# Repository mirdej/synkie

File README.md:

The Synkie is a modular open source analog video processor, developed by Michael Egger, Max Egger and Flo Kaufmann. A bit like the venerable modular Moog synthesizer it lets you toy around with the signal using patch cables – but this time not producing sound but images. It is an instrument for video, a playground, a platform to explore new ways to transform a video signal. Synkie is still in development, we constantly develop new modules – and even the base specifications may still change over time. 

Synkie’s main goal is playability not image quality, even though we try to design each module as best as we can. But patching is done with 2mm laboratory cables – not shielded 75Ohm BNC cables as one would normally use for video. No, you can even use any blank wire and tinker around with the signal in real time on the sk90-breadboard module… The laboratory plugs can be stacked, so you can easily divide the signal into multiple paths, feeding multiple modules at once and change the configuration on the fly. The resulting image can get quite messy down the road, but that’s part of the fun, or maybe even the main purpose…

# Before building stuff from here yourself - read this:

This Github repository is our working space and not a DIY tutorial. Lots of stuff is completely outdated and/or poorly documented. Here are some important notes about the current state of things (Oct 2021):

- Pretty much everything in the EAGLE directory is totally obsolete and we only keep it for documentation.

- We settled on the LMH6643 as our Opamp of choice for almost everything where frequency response matters. Not all schematics reflect this. In most cases if there's an opamp named "generic opamp" or even "LM833" - we probably meant LMH6643.

- There are several modules where the supply connector is flipped. As we etch a lot of boards ourselves there is no silkscreen and we don't see the error. ALWAYS check the polarity !

- We live in PAL land. These modules have not beent tested with NTSC video. Some might need to be adapted slightly, some might even work better than here ;-)

If you have any questions contact <info@synkie.net>

# Basics

## Synkie Backbone
Modules sk000 to sk009 constitute the Synkie Backbone – handling Ins out Outs to the normal Video World. Input video is clamped (black level = GND) and stripped of timing signals and color burst. This signal can then be fed to any processing modules.
In the end , timing signals and a phase corrected color burst is cut back into the modified signal, in sync with the Genlock input.

### sk000-power
Power distribution to backbone modules and rack. +5V, GND, -5V.

### sk001-genlock-in

This module takes any standard video signal as input and generates all necessary timing signals for the Synkie system. The input is first backporch-clamped to GND and all active video is cut off. This black image can serve as a genlock for connected sources (cameras). Colorburst is output as a seperate signal and used to syncronise a quartz crystal that generates a continuous 4.4336Mhz subcarrier signal for the rgb modules. A LM1881 generates the digital sync signals: horizontal sync, vertical sync, backporch and odd/even.

### sk002-input

This modules takes any standard video signal, clamps black level to GND and strips off synctips and colorburst. (still in active debate: me thinks sk002 should apply a gain of 1.43 to bring the 0.7V white level up to 1V)

### sk003-output

This module takes any signal as its input (from DC to 10Mhz). The scale-bias section controls amplitude and dc-shift. The signal is then clipped hard between 0V and 1V. Finally the resyncer adds synctips and colorburst to make it look like a standard video signal. 
When using video as an input to the sk003 any processing beforehand can add some tiny delay - depending on how many modules the signal passes through -  which causes a phase shift in the signal that can alter or completely destroy color. That is why the burst signal from sk001 first goes through a sk004-burstshift (allpass filter) that lets correct the phase error before it gets cut back into the video signal.

## Synkie Signals

### Terminology
| Signal name | Waveform| Description  |Specs|
|---|---|---|---|
|Genlock||A video signal that serves as the master synchronisation signal. Can be routed through and used as an input.|-0.3V to 0.7V|
|Video||Standard PAL video signal|-0.3V to 0.7V|
|Sync| |Digital sync pulses: H-Sync, V-Sync, Backporch, Odd/Even|0V to 5V|
|Burst|| Colorburst only, AC coupled|ca. -0.1V to 0.1V|
|Siff| |Synkie signal. Can be anything, DC, CV, Audio or Video. 0V means black. 1V means white|-1V to 1V|

### The SIFF signal
Synkie's goal is to be able to mix all signals, be it control signals, audio or picture. You should be able to use a video image as control voltage for a VCO like you should be able to inject a sound into the video or watch a steady 0.256 volts.

* Siff signals are DC coupled. 0V means black. 1V means white.
* Siff signals can still be negative, meaning superblack or substracting signals !
* Siff signals can be loud - going beyond 1V and below -1V. The sk003-output module will finally limit the signal to 0-1V.
* Siff signals can range from DC (0Hz) to ca. 10Mhz

This has the following implications for synkie modules:

* All module inputs should be high-impedance, DC coupled and ESR protected.
* All module outputs should be low-impedance and DC coupled.
* Whenever possible a module's bandwidth should be at least 4Mhz
* Sensible CV range should be between 0V and 1V.
* But: Modules must be able to cope with voltages as low as -5V to as high as 5V
* Gate signals are 0V to 1V !!
* So: trigger inputs should trigger at around 0.5V ! Use comparators.

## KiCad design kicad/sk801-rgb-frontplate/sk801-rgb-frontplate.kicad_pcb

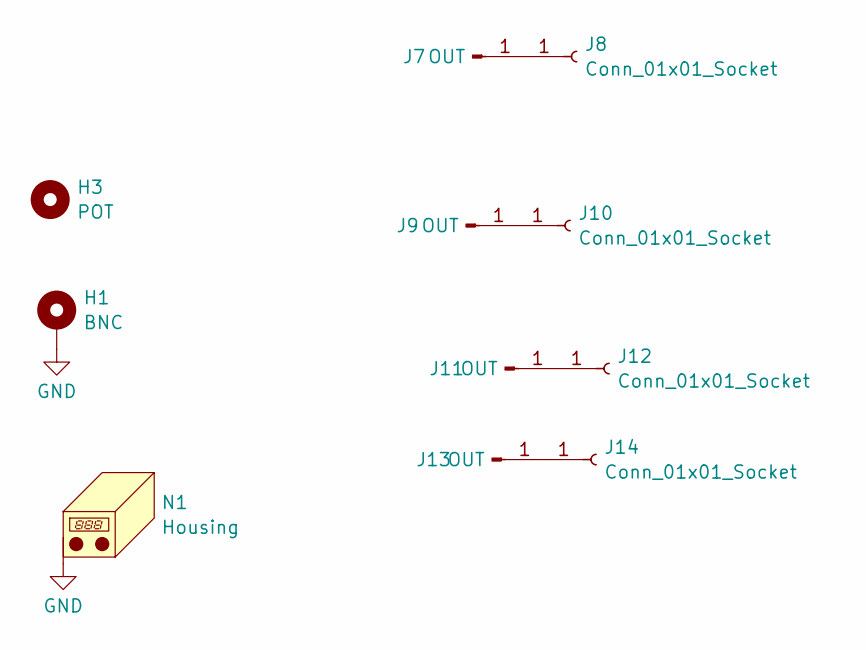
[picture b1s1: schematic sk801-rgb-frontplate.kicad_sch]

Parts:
H1: BNC; BNC_Ali_Frontplate
H3: POT; PotentiometerNournsPRS12Frontplate
J7, J9, J11, J13: OUT; Banana2mm-Löthülse
J8, J10, J12, J14: Conn_01x01_Socket; smd-1pin
N1: Housing; Frontplate_20mm

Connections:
GND: H1.1 (1_1), N1.1 (PAD_1)
unnamed: J7.1 (Pin_1_1), J8.1 (Pin_1_1)
unnamed: J9.1 (Pin_1_1), J10.1 (Pin_1_1)
unnamed: J11.1 (Pin_1_1), J12.1 (Pin_1_1)
unnamed: J13.1 (Pin_1_1), J14.1 (Pin_1_1)

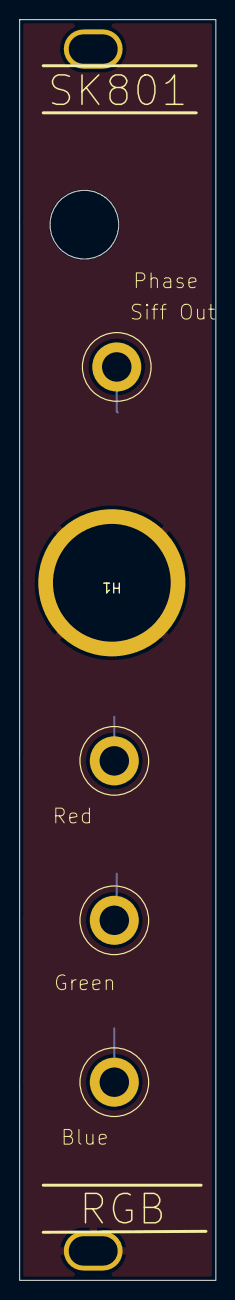
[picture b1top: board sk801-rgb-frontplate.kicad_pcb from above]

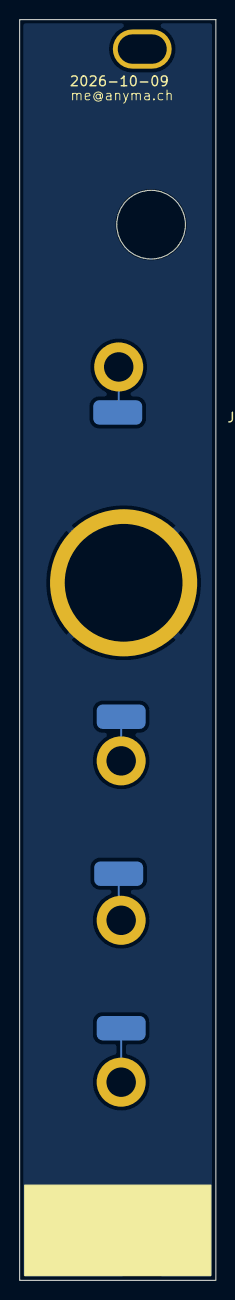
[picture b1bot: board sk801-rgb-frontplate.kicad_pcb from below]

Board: 2 copper layers, 20.0 x 128.5 mm, 11 parts (4 on the bottom side), 5 nets.

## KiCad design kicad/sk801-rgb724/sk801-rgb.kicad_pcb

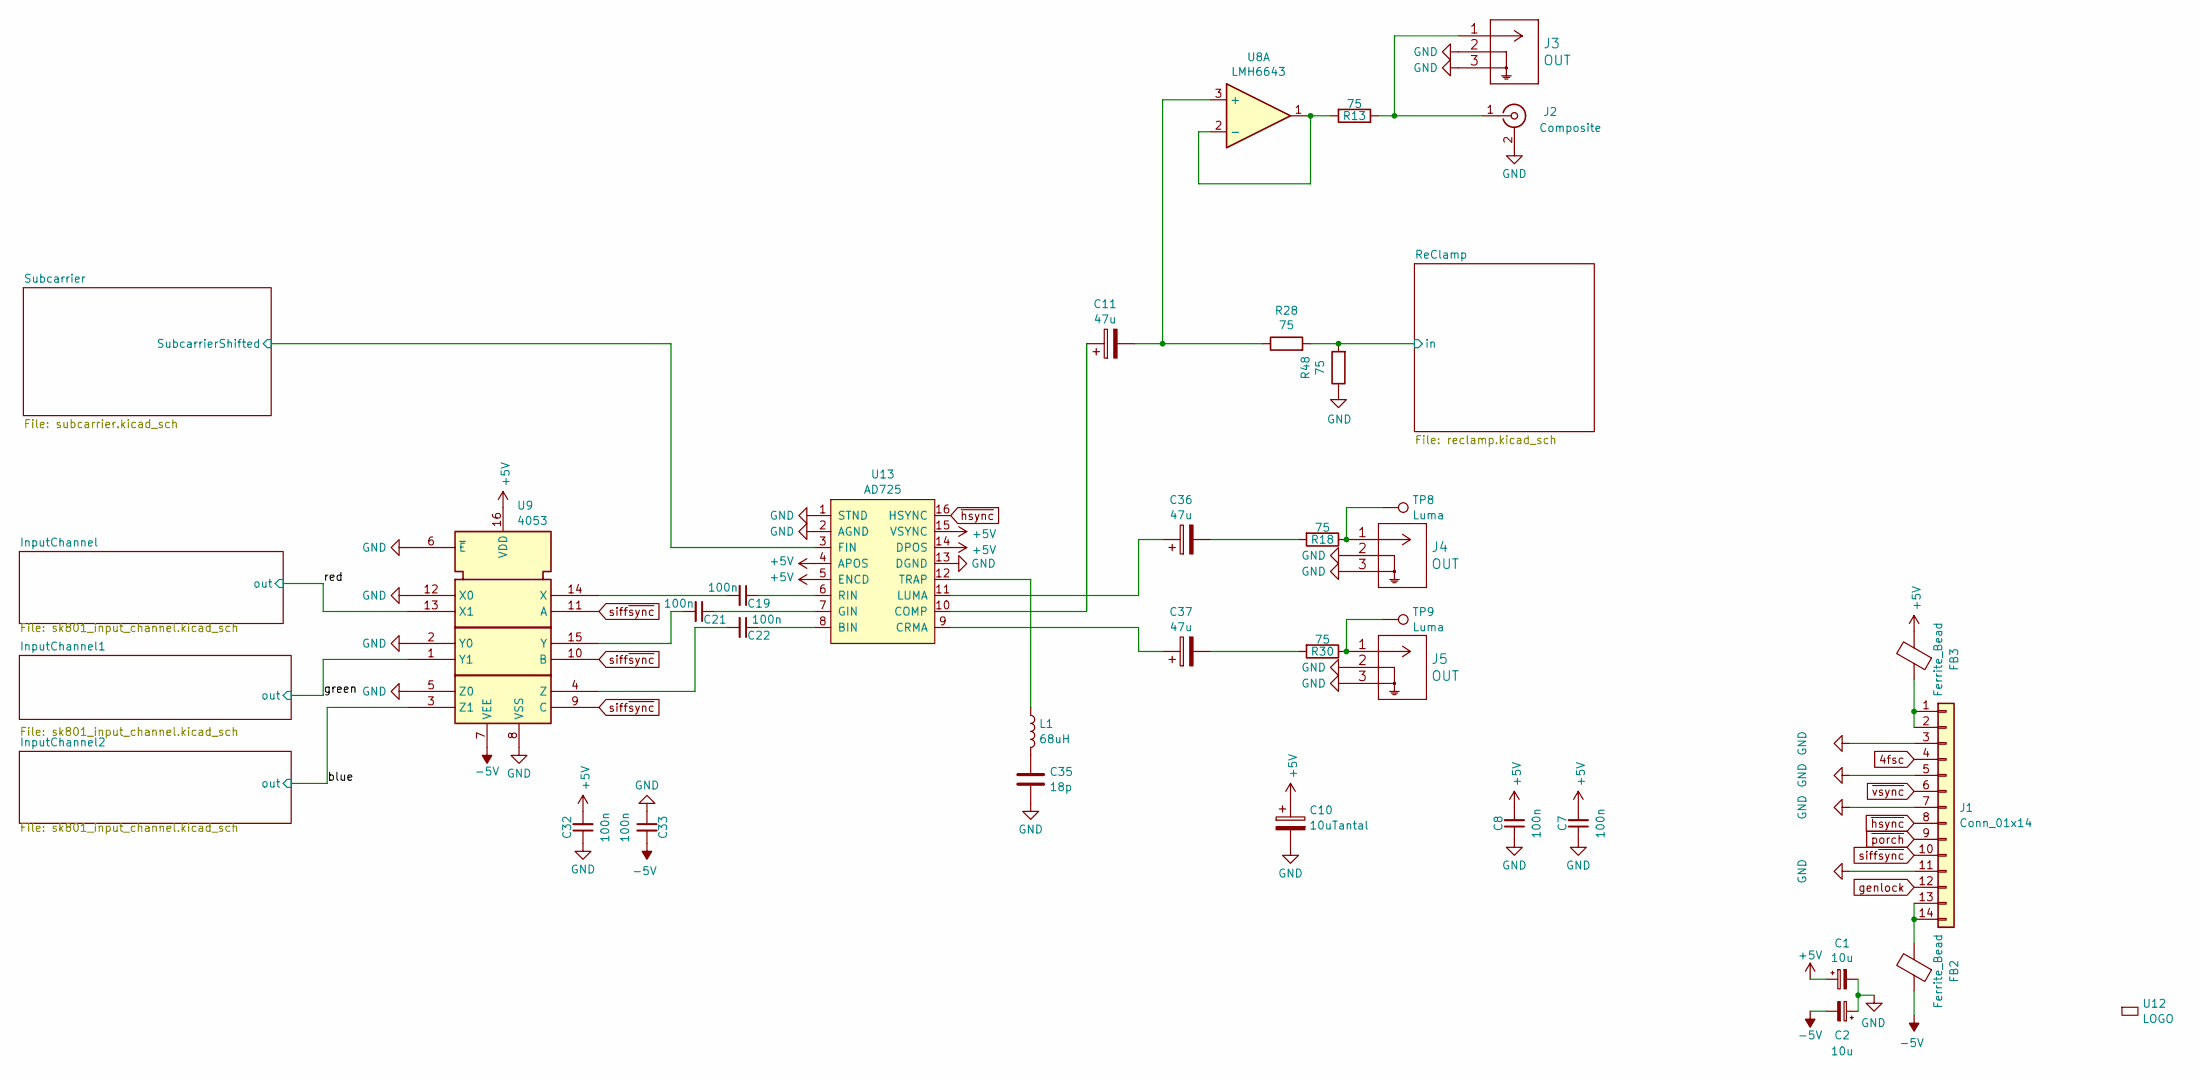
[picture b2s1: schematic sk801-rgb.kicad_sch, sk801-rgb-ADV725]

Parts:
C1, C2: 10u; C_0805_2012Metric; LCSC C15850
C7, C8, C19, C21, C22, C32, C33: 100n; C_0402_1005Metric; LCSC C1525
C10: 10uTantal; CP_EIA-3216-18_Kemet-A; LCSC C7171
C11, C36, C37: 47u; C_1206_3216Metric; LCSC C96123
C35: 18p; C_0603_1608Metric; LCSC C1647
FB2, FB3: Ferrite_Bead; L_0805_2012Metric; LCSC C1017
J1: Conn_01x14; SYNKIE-BUS.v3
J2: Composite; BNC_Aliexpress
J3, J4, J5: OUT; TE_UMCC_2337019-1; LCSC C5137195
L1: 68uH; L_APV_APH0420; LCSC C2929423
R13, R18, R28, R30, R48: 75; R_0603_1608Metric; LCSC C4275
TP8, TP9: Luma; TestPoint_THTPad_D4.0mm_Drill2.0mm
U8: LMH6643; VSSOP-8_3x3mm_P0.65mm; LCSC C478382
U9: 4053; SOIC-16_3.9x9.9mm_P1.27mm; LCSC C7500846
U12: LOGO; logo_anyma
U13: AD725; SOIC-16W_7.5x10.3mm_P1.27mm

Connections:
4fsc: J1.4; also elsewhere on the board
+5V: C1.1, C7.2, C8.2, C10.1, C32.2, FB3.2, U9.16 (VDD), U13.4 (APOS), U13.5 (ENCD), U13.14 (DPOS), U13.15 (VSYNC); also elsewhere on the board
-5V: C2.2, C33.2, FB2.1, U9.7 (VEE); also elsewhere on the board
/ReClamp/in: R28.2, R48.2; also elsewhere on the board
/Subcarrier/SubcarrierShifted: U13.3 (FIN); also elsewhere on the board
/blue: U9.3 (Z1); also elsewhere on the board
/green: U9.1 (Y1); also elsewhere on the board
/red: U9.13 (X1); also elsewhere on the board
GND: C1.2, C2.1, C7.1, C8.1, C10.2, C32.1, C33.1, C35.2, J1.3, J1.5, J1.7, J1.11, J2.2 (Ext), J3.2, J3.3, J4.2, J4.3, J5.2, J5.3, R48.1, U9.2 (Y0), U9.5 (Z0), U9.6 (~E), U9.8 (VSS), U9.12 (X0), U13.1 (STND), U13.2 (AGND), U13.13 (DGND); also elsewhere on the board
unnamed: C35.1, L1.2
unnamed: C36.2, R18.2
unnamed: C37.2, R30.2
unnamed: FB3.1, J1.1, J1.2
unnamed: FB2.2, J1.13, J1.14
unnamed: J2.1 (In), J3.1, R13.1
unnamed: J4.1, R18.1, TP8.1 (1_1)
unnamed: J5.1, R30.1, TP9.1 (1_1)
unnamed: C11.2, R28.1, U8.3 (+)
unnamed: R13.2, U8.1, U8.2 (-)
unnamed: C19.2, U9.14 (X)
unnamed: C21.2, U9.15 (Y)
unnamed: C22.2, U9.4 (Z)
unnamed: C22.1, U13.8 (BIN)
unnamed: C11.1, U13.10 (COMP)
unnamed: C37.1, U13.9 (CRMA)
unnamed: C21.1, U13.7 (GIN)
unnamed: C36.1, U13.11 (LUMA)
unnamed: C19.1, U13.6 (RIN)
unnamed: L1.1, U13.12 (TRAP)
genlock: J1.12
siff~sync: J1.10, U9.9 (C), U9.10 (B), U9.11 (A); also elsewhere on the board
~hsync: J1.8, U13.16 (HSYNC)
~porch: J1.9; also elsewhere on the board
~vsync: J1.6

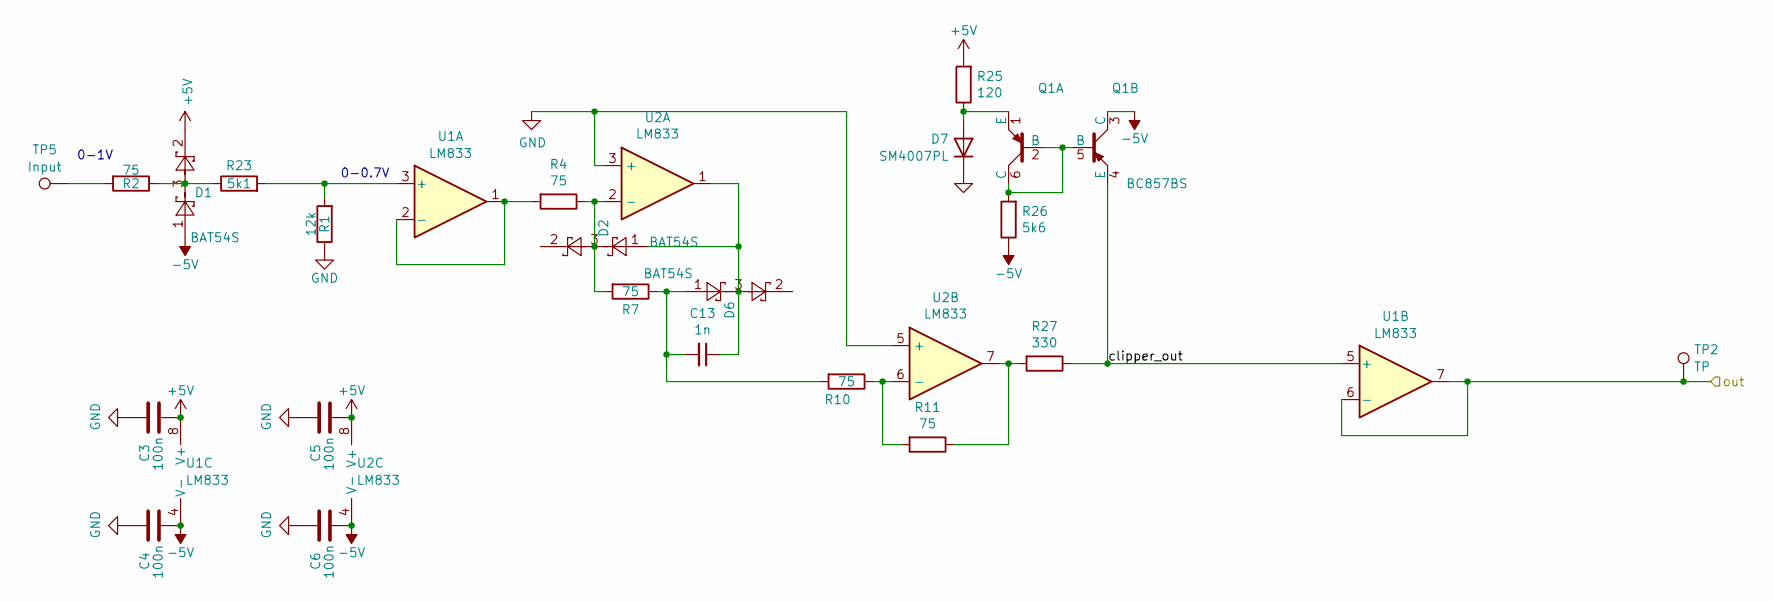
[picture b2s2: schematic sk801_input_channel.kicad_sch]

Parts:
C3, C4, C5, C6: 100n; C_0402_1005Metric; LCSC C1525
C13: 1n; C_0603_1608Metric; LCSC C1588
D1, D2, D6: BAT54S; SOT-23; LCSC C7420333
D7: SM4007PL; D_SOD-123F; LCSC C64898
Q1: BC857BS; SOT-363_SC-70-6_Handsoldering; LCSC C22381405
R1: 12k; R_0603_1608Metric; LCSC C22790
R2, R4, R7, R10, R11: 75; R_0603_1608Metric; LCSC C4275
R23: 5k1; R_0603_1608Metric; LCSC C23186
R25: 120; R_0603_1608Metric; LCSC C22787
R26: 5k6; R_0603_1608Metric; LCSC C23189
R27: 330; R_0603_1608Metric; LCSC C23138
TP2: TP; TestPoint_Pad_D2.0mm
TP5: Input; TestPoint_THTPad_D4.0mm_Drill2.0mm
U1, U2: LM833; SOIC-8_3.9x4.9mm_P1.27mm; LCSC C7969

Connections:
+5V: C3.2, C5.2, D1.2, R25.2, U1.8 (V+), U2.8 (V+); also elsewhere on the board
-5V: C4.2, C6.2, D1.1, Q1.3 (C), R26.1, U1.4 (V-), U2.4 (V-); also elsewhere on the board
/InputChannel/clipper_out: Q1.4 (E), R27.1, U1.5 (+)
/red: TP2.1 (1_1), U1.6 (-), U1.7; also elsewhere on the board
GND: C3.1, C4.1, C5.1, C6.1, D7.1 (K), R1.1, U2.3 (+), U2.5 (+); also elsewhere on the board
unnamed: C13.1, D2.1, D6.3, U2.1
unnamed: C13.2, D6.1, R7.1, R10.2
unnamed: D1.3, R2.1, R23.1
unnamed: D7.2 (A), Q1.1 (E), R25.1
unnamed: Q1.2 (B), Q1.5 (B), Q1.6 (C), R26.2
unnamed: R2.2, TP5.1 (1_1)
unnamed: R11.1, R27.2, U2.7
unnamed: R1.2, R23.2, U1.3 (+)
unnamed: R4.2, U1.1, U1.2 (-)
unnamed: D2.3, R4.1, R7.2, U2.2 (-)
unnamed: R10.1, R11.2, U2.6 (-)

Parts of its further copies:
C14, C15, C16, C18, C25, C26, C27, C28: 100n; C_0402_1005Metric; LCSC C1525
C23, C30: 1n; C_0603_1608Metric; LCSC C1588
D3, D4, D5, D8, D10, D11: BAT54S; SOT-23; LCSC C7420333
D9, D12: SM4007PL; D_SOD-123F; LCSC C64898
Q2, Q3: BC857BS; SOT-363_SC-70-6_Handsoldering; LCSC C22381405
R5, R16: 12k; R_0603_1608Metric; LCSC C22790
R6, R9, R12, R14, R15, R17, R19, R20, R21, R22: 75; R_0603_1608Metric; LCSC C4275
R24, R42: 5k1; R_0603_1608Metric; LCSC C23186
R37, R43: 120; R_0603_1608Metric; LCSC C22787
R38, R44: 5k6; R_0603_1608Metric; LCSC C23189
R39, R45: 330; R_0603_1608Metric; LCSC C23138
TP3, TP4: TP; TestPoint_Pad_D2.0mm
TP6, TP7: Input; TestPoint_THTPad_D4.0mm_Drill2.0mm
U3, U5, U6, U7: LM833; SOIC-8_3.9x4.9mm_P1.27mm; LCSC C7969

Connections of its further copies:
+5V: C14.2, C16.2, C25.2, C27.2, D3.2, D5.2, R37.2, R43.2, U3.8 (V+), U5.8 (V+), U6.8 (V+), U7.8 (V+); also elsewhere on the board
-5V: C15.2, C18.2, C26.2, C28.2, D3.1, D5.1, Q2.3 (C), Q3.3 (C), R38.1, R44.1, U3.4 (V-), U5.4 (V-), U6.4 (V-), U7.4 (V-); also elsewhere on the board
/InputChannel1/clipper_out: Q2.4 (E), R39.1, U3.5 (+)
/InputChannel2/clipper_out: Q3.4 (E), R45.1, U6.5 (+)
/blue: TP4.1 (1_1), U6.6 (-), U6.7; also elsewhere on the board
/green: TP3.1 (1_1), U3.6 (-), U3.7; also elsewhere on the board
GND: C14.1, C15.1, C16.1, C18.1, C25.1, C26.1, C27.1, C28.1, D9.1 (K), D12.1 (K), R5.1, R16.1, U5.3 (+), U5.5 (+), U7.3 (+), U7.5 (+); also elsewhere on the board
unnamed: C23.1, D4.1, D8.3, U5.1
unnamed: C23.2, D8.1, R12.1, R14.2
unnamed: C30.1, D10.1, D11.3, U7.1
unnamed: C30.2, D11.1, R20.1, R21.2
unnamed: D3.3, R6.1, R24.1
unnamed: D5.3, R17.1, R42.1
unnamed: D9.2 (A), Q2.1 (E), R37.1
unnamed: D12.2 (A), Q3.1 (E), R43.1
unnamed: Q2.2 (B), Q2.5 (B), Q2.6 (C), R38.2
unnamed: Q3.2 (B), Q3.5 (B), Q3.6 (C), R44.2
unnamed: R6.2, TP6.1 (1_1)
unnamed: R15.1, R39.2, U5.7
unnamed: R17.2, TP7.1 (1_1)
unnamed: R22.1, R45.2, U7.7
unnamed: R5.2, R24.2, U3.3 (+)
unnamed: R9.2, U3.1, U3.2 (-)
unnamed: D4.3, R9.1, R12.2, U5.2 (-)
unnamed: R14.1, R15.2, U5.6 (-)
unnamed: R16.2, R42.2, U6.3 (+)
unnamed: R19.2, U6.1, U6.2 (-)
unnamed: D10.3, R19.1, R20.2, U7.2 (-)
unnamed: R21.1, R22.2, U7.6 (-)

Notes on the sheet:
0-0.7V
0-1V

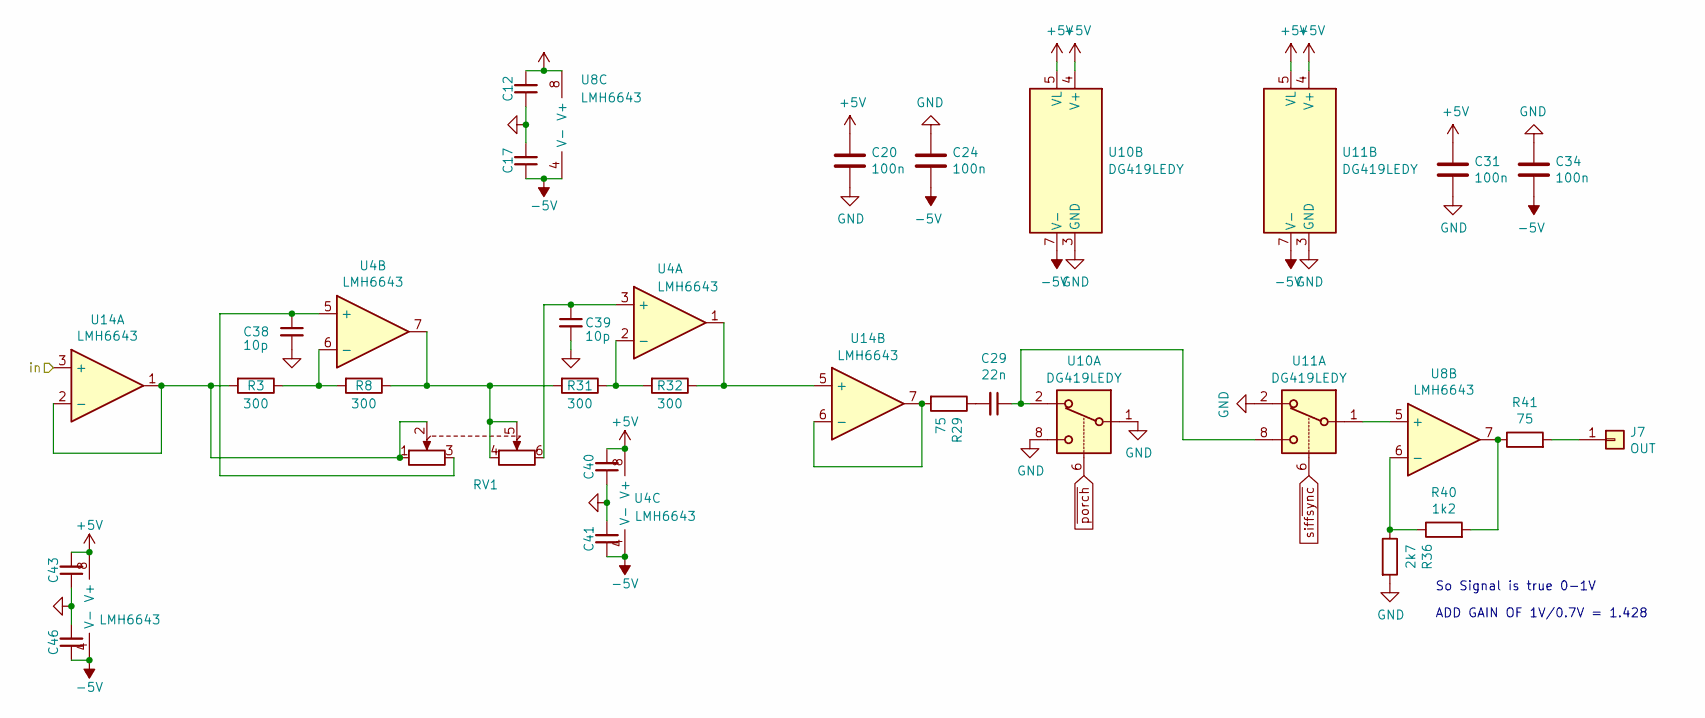
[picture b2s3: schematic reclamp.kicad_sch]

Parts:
C12, C17, C20, C24, C31, C34, C40, C41, C43, C46: 100n; C_0402_1005Metric; LCSC C1525
C29: 22n; C_0603_1608Metric; LCSC C21122
C38, C39: 10p; C_0603_1608Metric; LCSC C1634
J7: OUT; TestPoint_THTPad_D4.0mm_Drill2.0mm
R3, R8, R31, R32: 300; R_0603_1608Metric; LCSC C23025
R29, R41: 75; R_0603_1608Metric; LCSC C4275
R36: 2k7; R_0603_1608Metric; LCSC C13167
R40: 1k2; R_0603_1608Metric; LCSC C22765
RV1: PRS12R-2
U4, U8, U14: LMH6643; VSSOP-8_3x3mm_P0.65mm; LCSC C478382
U10, U11: DG419LEDY; SOIC-8_3.9x4.9mm_P1.27mm; LCSC C2673265

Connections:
+5V: C12.2, C20.1, C31.1, C40.2, C43.2, U4.8 (V+), U8.8 (V+), U10.4 (V+), U10.5 (VL), U11.4 (V+), U11.5 (VL), U14.8 (V+); also elsewhere on the board
-5V: C17.1, C24.2, C34.2, C41.1, C46.1, U4.4 (V-), U8.4 (V-), U10.7 (V-), U11.7 (V-), U14.4 (V-); also elsewhere on the board
/ReClamp/in: U14.3 (+); also elsewhere on the board
GND: C12.1, C17.2, C20.2, C24.1, C31.2, C34.1, C38.2, C39.2, C40.1, C41.2, C43.1, C46.2, R36.2, U10.1, U10.3 (GND), U10.8, U11.2, U11.3 (GND); also elsewhere on the board
unnamed: C29.1, U10.2, U11.8
unnamed: C29.2, R29.1
unnamed: J7.1 (Pin_1_1), R41.2
unnamed: R8.1, R31.2, RV1.4, RV1.5, U4.7
unnamed: R40.2, R41.1, U8.7
unnamed: C39.1, RV1.6, U4.3 (+)
unnamed: R31.1, R32.2, U4.2 (-)
unnamed: C38.1, RV1.3, U4.5 (+)
unnamed: R3.1, R8.2, U4.6 (-)
unnamed: U8.5 (+), U11.1
unnamed: R36.1, R40.1, U8.6 (-)
unnamed: R3.2, RV1.1, RV1.2, U14.1, U14.2 (-)
unnamed: R32.1, U4.1, U14.5 (+)
unnamed: R29.2, U14.6 (-), U14.7
siff~sync: U11.6; also elsewhere on the board
~porch: U10.6; also elsewhere on the board

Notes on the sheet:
ADD GAIN OF 1V/0.7V = 1.428
So Signal is true 0-1V

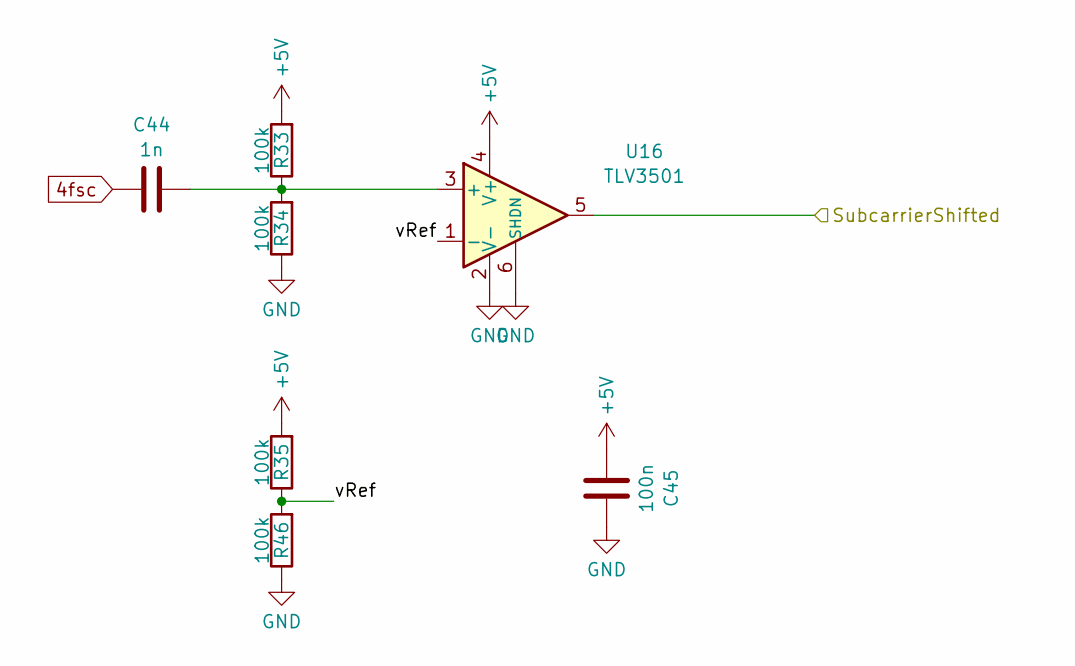
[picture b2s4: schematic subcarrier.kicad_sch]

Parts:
C44: 1n; C_0603_1608Metric; LCSC C1588
C45: 100n; C_0402_1005Metric; LCSC C1525
R33, R34, R35, R46: 100k; R_0603_1608Metric; LCSC C25803
U16: TLV3501; SOT-23-6; LCSC C133251

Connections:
4fsc: C44.1; also elsewhere on the board
+5V: C45.1, R33.2, R35.2, U16.4 (V+); also elsewhere on the board
/Subcarrier/SubcarrierShifted: U16.5; also elsewhere on the board
/Subcarrier/vRef: R35.1, R46.2, U16.1 (-)
GND: C45.2, R34.1, R46.1, U16.2 (V-), U16.6 (SHDN); also elsewhere on the board
unnamed: C44.2, R33.1, R34.2, U16.3 (+)

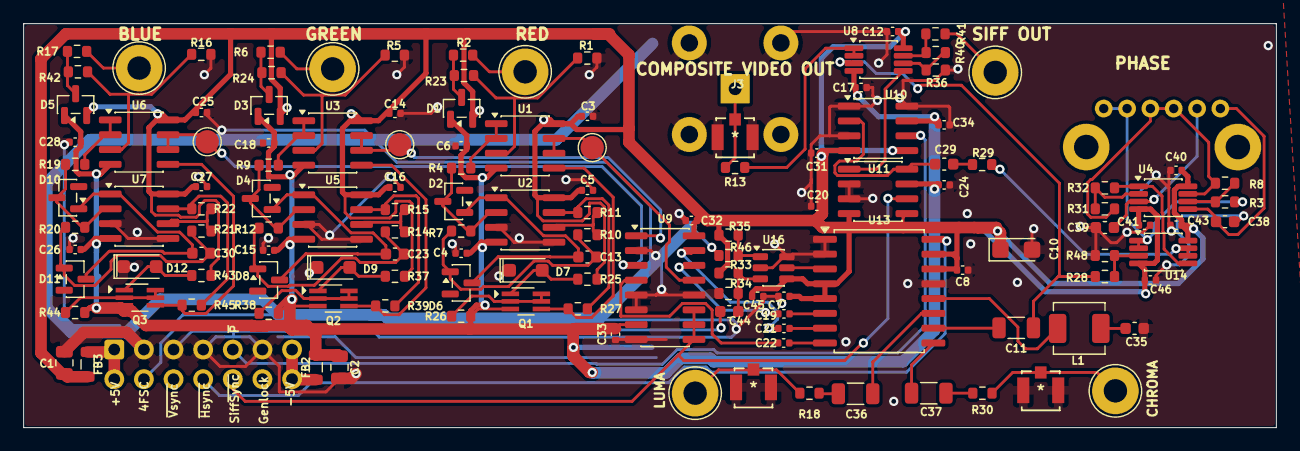
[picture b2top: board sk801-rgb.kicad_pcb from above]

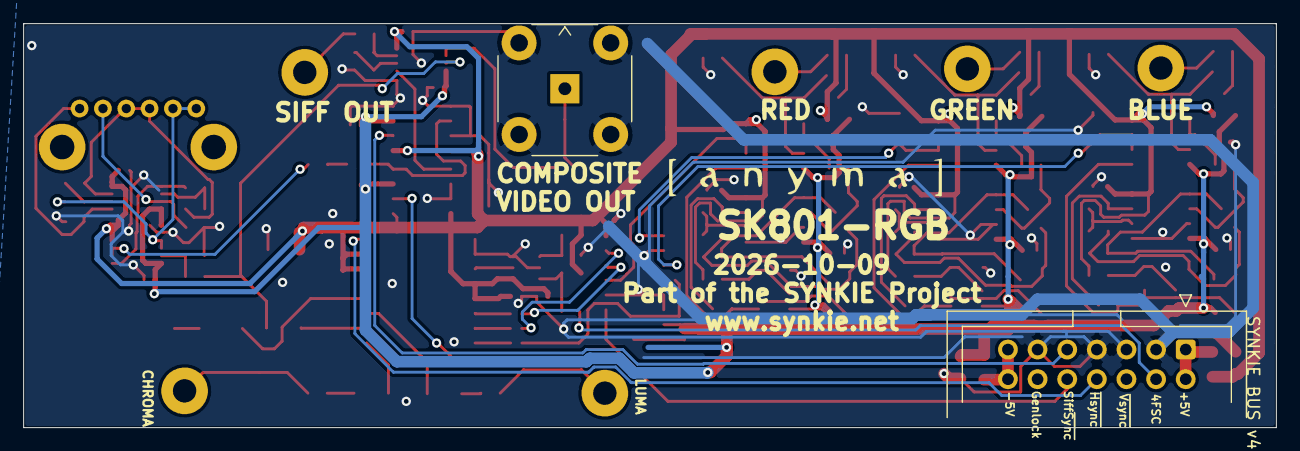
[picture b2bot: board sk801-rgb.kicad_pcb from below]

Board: 2 copper layers, 107.4 x 34.6 mm, 139 parts (4 on the bottom side), 84 nets.

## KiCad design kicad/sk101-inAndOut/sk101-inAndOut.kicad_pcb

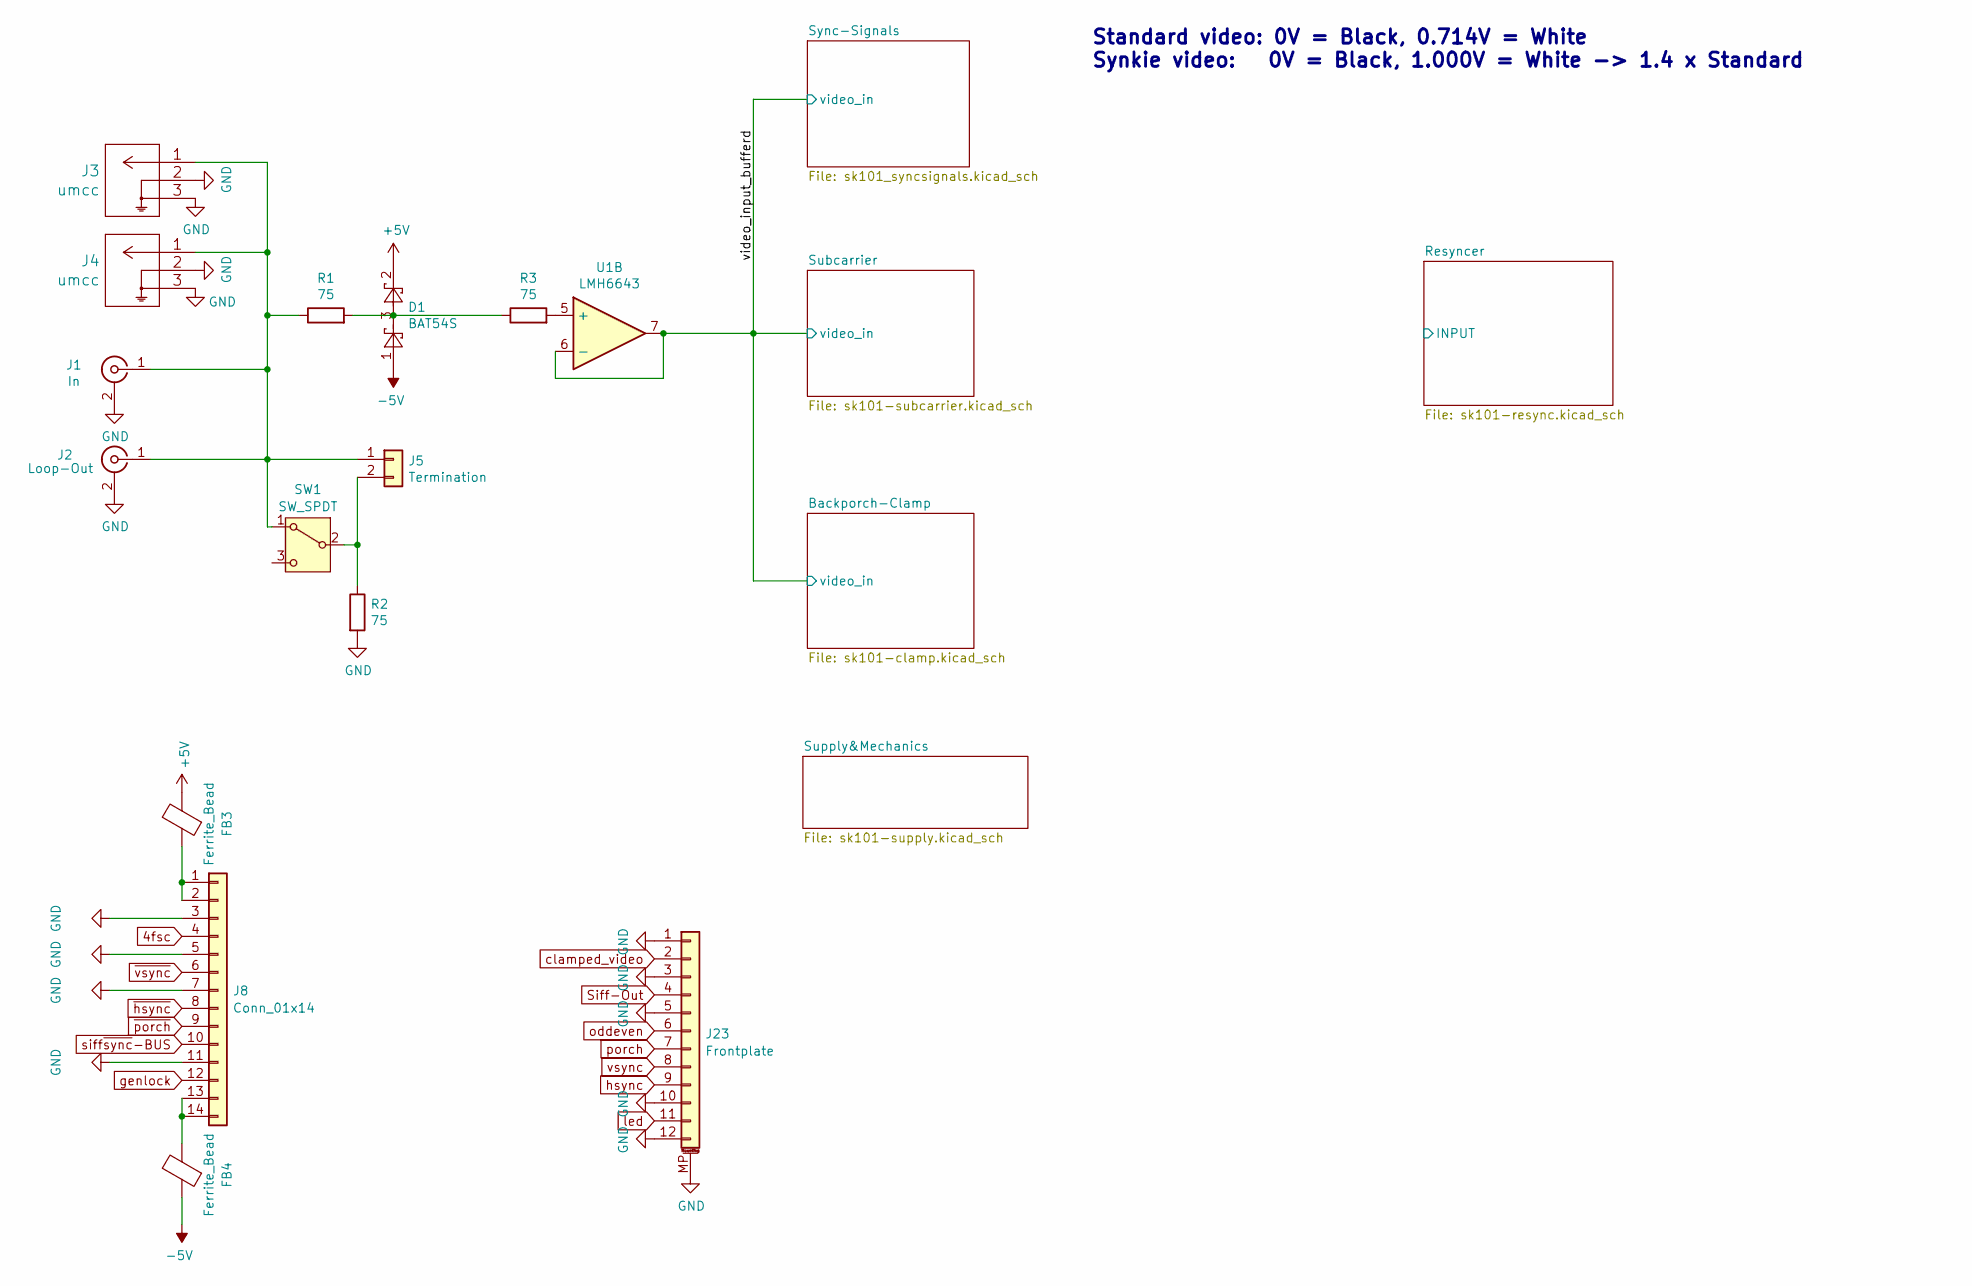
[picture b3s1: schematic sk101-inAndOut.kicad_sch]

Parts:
D1: BAT54S; SOT-23; LCSC C7420333
FB3, FB4: Ferrite_Bead; L_0805_2012Metric; LCSC C1017
J1: In; BNC_Aliexpress
J2: Loop-Out; BNC_Aliexpress
J3, J4: umcc; TE_UMCC_2337019-1; LCSC C5137195
J5: Termination; PinHeader_1x02_P2.54mm_Vertical
J8: Conn_01x14; SYNKIE-BUS.v3
J23: Frontplate; AFC04-S12FCC-00; LCSC C21275
R1, R2, R3: 75; R_0603_1608Metric; LCSC C4275
SW1: SW_SPDT; CUS-12TB_NDC; LCSC C109335
U1: LMH6643; VSSOP-8_3x3mm_P0.65mm; LCSC C478382

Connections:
4fsc: J8.4; also elsewhere on the board
+5V: D1.2, FB3.2; also elsewhere on the board
-5V: D1.1, FB4.1; also elsewhere on the board
/video_input_bufferd: U1.6 (-), U1.7; also elsewhere on the board
GND: J1.2 (Ext), J2.2 (Ext), J3.2, J3.3, J4.2, J4.3, J8.3, J8.5, J8.7, J8.11, J23.1, J23.3, J23.5, J23.10, J23.12, J23.MP (MountPin), R2.2; also elsewhere on the board
unnamed: D1.3, R1.2, R3.1
unnamed: J1.1 (In), J2.1 (In), J3.1, J4.1, J5.1, R1.1, SW1.1 (A)
unnamed: J5.2, R2.1, SW1.2 (B)
unnamed: FB3.1, J8.1, J8.2
unnamed: FB4.2, J8.13, J8.14
unnamed: R3.2, U1.5 (+)
Siff-Out: J23.4; also elsewhere on the board
clamped_video: J23.2; also elsewhere on the board
genlock: J8.12; also elsewhere on the board
hsync: J23.9; also elsewhere on the board
led: J23.11; also elsewhere on the board
oddeven: J23.6; also elsewhere on the board
porch: J23.7; also elsewhere on the board
siff~sync-BUS: J8.10; also elsewhere on the board
vsync: J23.8; also elsewhere on the board
~hsync: J8.8; also elsewhere on the board
~porch: J8.9; also elsewhere on the board
~vsync: J8.6; also elsewhere on the board

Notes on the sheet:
Standard video: 0V = Black, 0.714V = White Synkie video: 0V = Black, 1.000V = White -> 1.4 x Standard

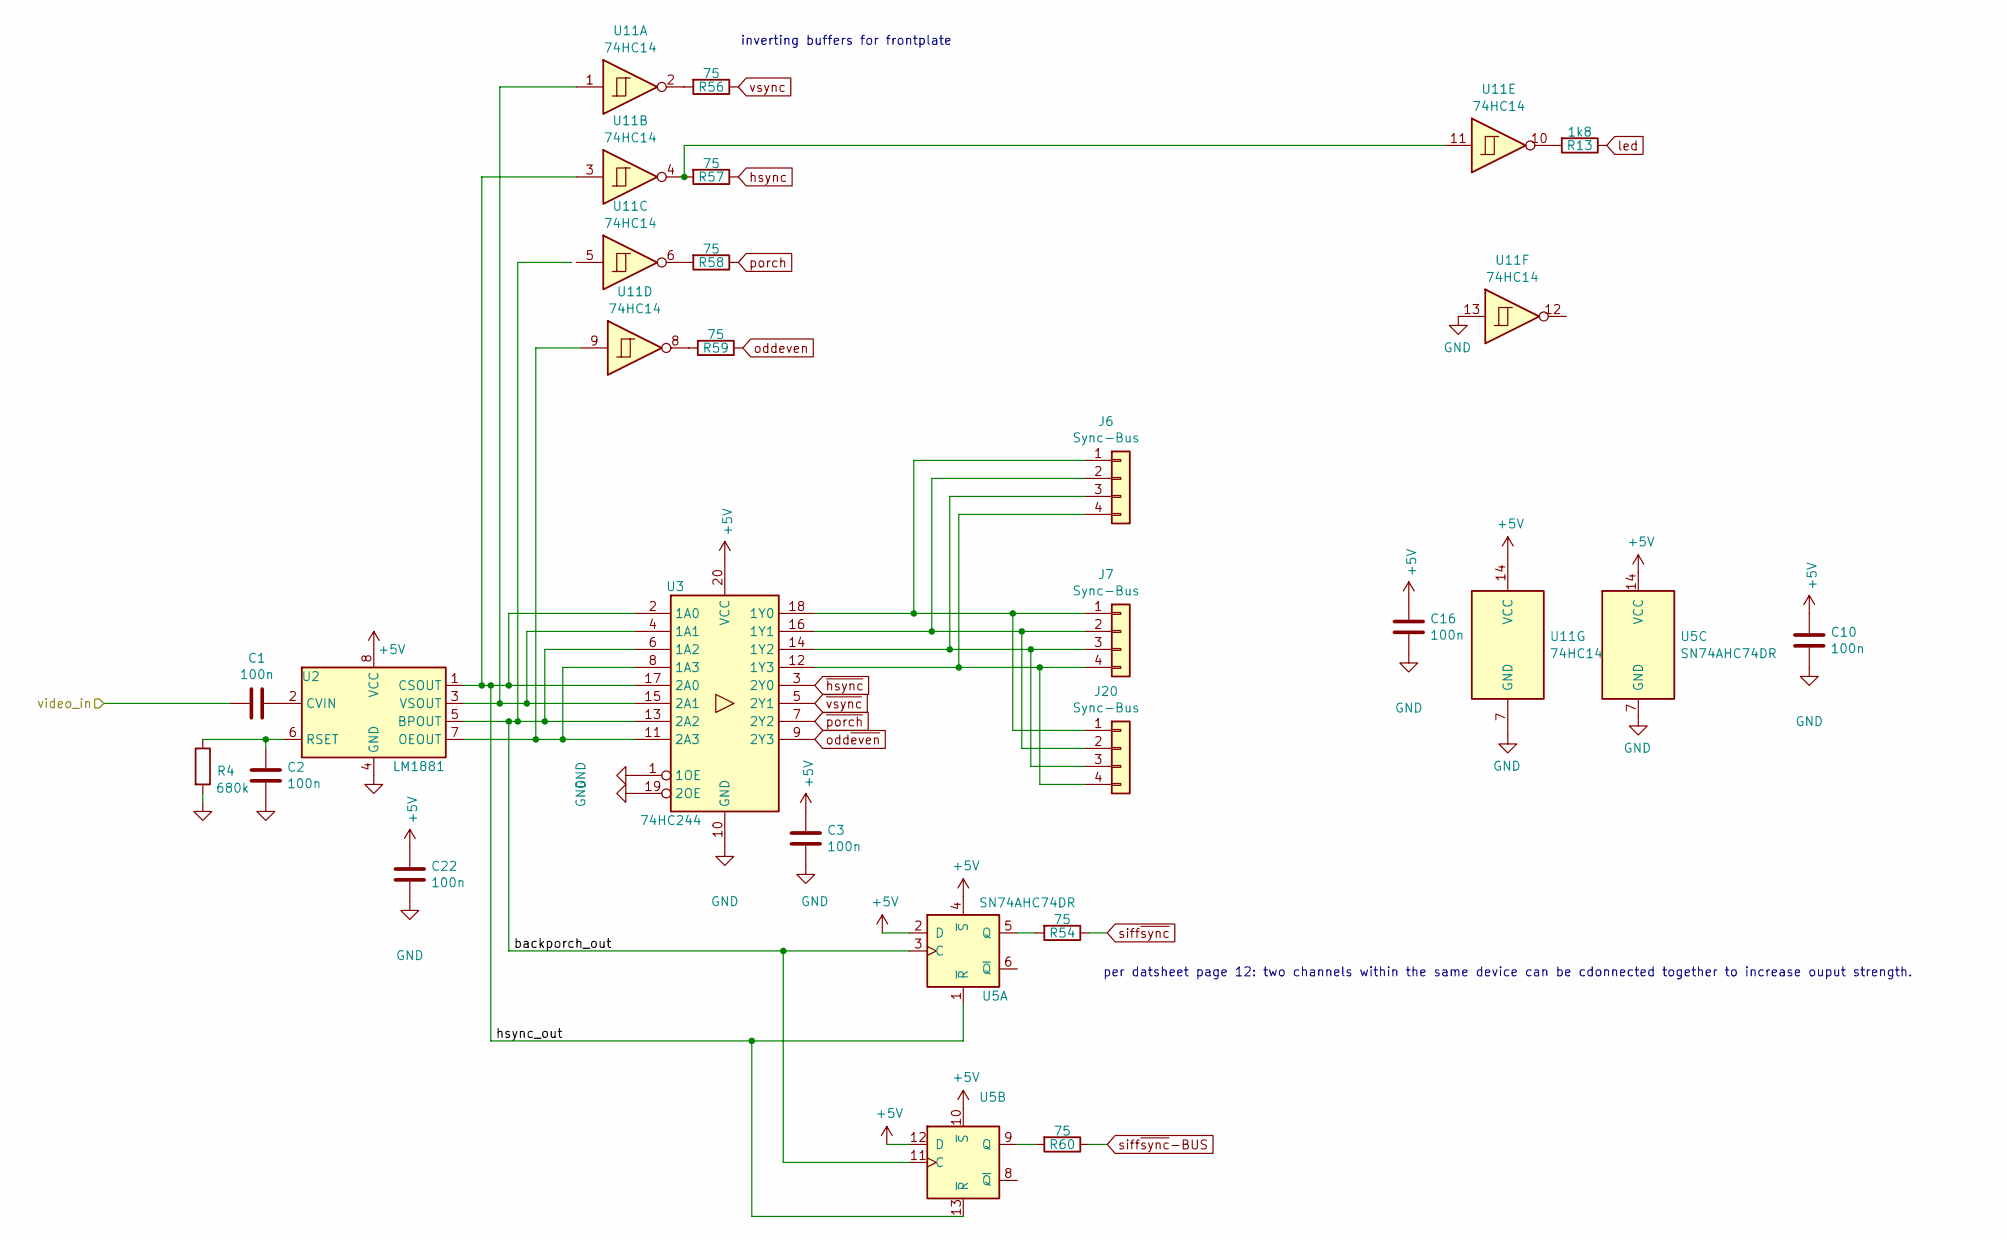
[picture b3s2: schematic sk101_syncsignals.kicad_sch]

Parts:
C1, C2, C3, C10, C16, C22: 100n; C_0603_1608Metric; LCSC C14663
J6, J7: Sync-Bus; Hirose_DF13-04P-1.25DSA_1x04_P1.25mm_Vertical; LCSC C17617036
J20: Sync-Bus; Molex_KK-254_AE-6410-04A_1x04_P2.54mm_Vertical; LCSC C17617036
R4: 680k; R_0603_1608Metric; LCSC C25822
R13: 1k8; R_0603_1608Metric; LCSC C4177
R54, R56, R57, R58, R59, R60: 75; R_0603_1608Metric; LCSC C4275
U2: LM1881; SOIC-8_3.9x4.9mm_P1.27mm; LCSC C518922
U3: 74HC244; SO-20_12.8x7.5mm_P1.27mm; LCSC C5622
U5: SN74AHC74DR; SOIC-14_3.9x8.7mm_P1.27mm; LCSC C7621
U11: 74HC14; SOIC-14_3.9x8.7mm_P1.27mm; LCSC C5605

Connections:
+5V: C3.1, C10.1, C16.1, C22.1, U2.8 (VCC), U3.20 (VCC), U5.2 (D), U5.4 (~S), U5.10 (~S), U5.12 (D), U5.14 (VCC), U11.14 (VCC); also elsewhere on the board
/Sync-Signals/backporch_out: U2.5 (BPOUT), U3.6 (1A2), U3.13 (2A2), U5.3 (C), U5.11 (C)
/Sync-Signals/hsync_out: U2.1 (CSOUT), U3.2 (1A0), U3.17 (2A0), U5.1 (~R), U5.13 (~R), U11.3
/video_input_bufferd: C1.2; also elsewhere on the board
GND: C2.2, C3.2, C10.2, C16.2, C22.2, R4.2, U2.4 (GND), U3.1 (1OE), U3.10 (GND), U3.19 (2OE), U5.7 (GND), U11.7 (GND), U11.13; also elsewhere on the board
unnamed: J6.1, J7.1, J20.1, U3.18 (1Y0)
unnamed: J6.2, J7.2, J20.2, U3.16 (1Y1)
unnamed: J6.3, J7.3, J20.3, U3.14 (1Y2)
unnamed: J6.4, J7.4, J20.4, U3.12 (1Y3)
unnamed: R13.2, U11.10
unnamed: R56.2, U11.2
unnamed: R57.2, U11.4, U11.11
unnamed: R58.2, U11.6
unnamed: R59.2, U11.8
unnamed: C1.1, U2.2 (CVIN)
unnamed: U2.7 (OEOUT), U3.8 (1A3), U3.11 (2A3), U11.9
unnamed: C2.1, R4.1, U2.6 (RSET)
unnamed: U2.3 (VSOUT), U3.4 (1A1), U3.15 (2A1), U11.1
unnamed: R54.2, U5.5 (Q)
unnamed: R60.2, U5.9 (Q)
hsync: R57.1; also elsewhere on the board
led: R13.1; also elsewhere on the board
oddeven: R59.1; also elsewhere on the board
odd~even: U3.9 (2Y3)
porch: R58.1; also elsewhere on the board
siff~sync: R54.1; also elsewhere on the board
siff~sync-BUS: R60.1; also elsewhere on the board
vsync: R56.1; also elsewhere on the board
~hsync: U3.3 (2Y0); also elsewhere on the board
~porch: U3.7 (2Y2); also elsewhere on the board
~vsync: U3.5 (2Y1); also elsewhere on the board

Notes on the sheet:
inverting buffers for frontplate
per datsheet page 12: two channels within the same device can be cdonnected together to increase ouput strength.

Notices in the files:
parts and their libraries:
Copyright 2016 Accelerated Designs. All rights reserved.
